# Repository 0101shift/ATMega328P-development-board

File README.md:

# ATMega328P-development-board
A development board designed to test ATMega328P Micro-controller which is similar to Arduino UNO. This was my very first Board design that i did in my college days.

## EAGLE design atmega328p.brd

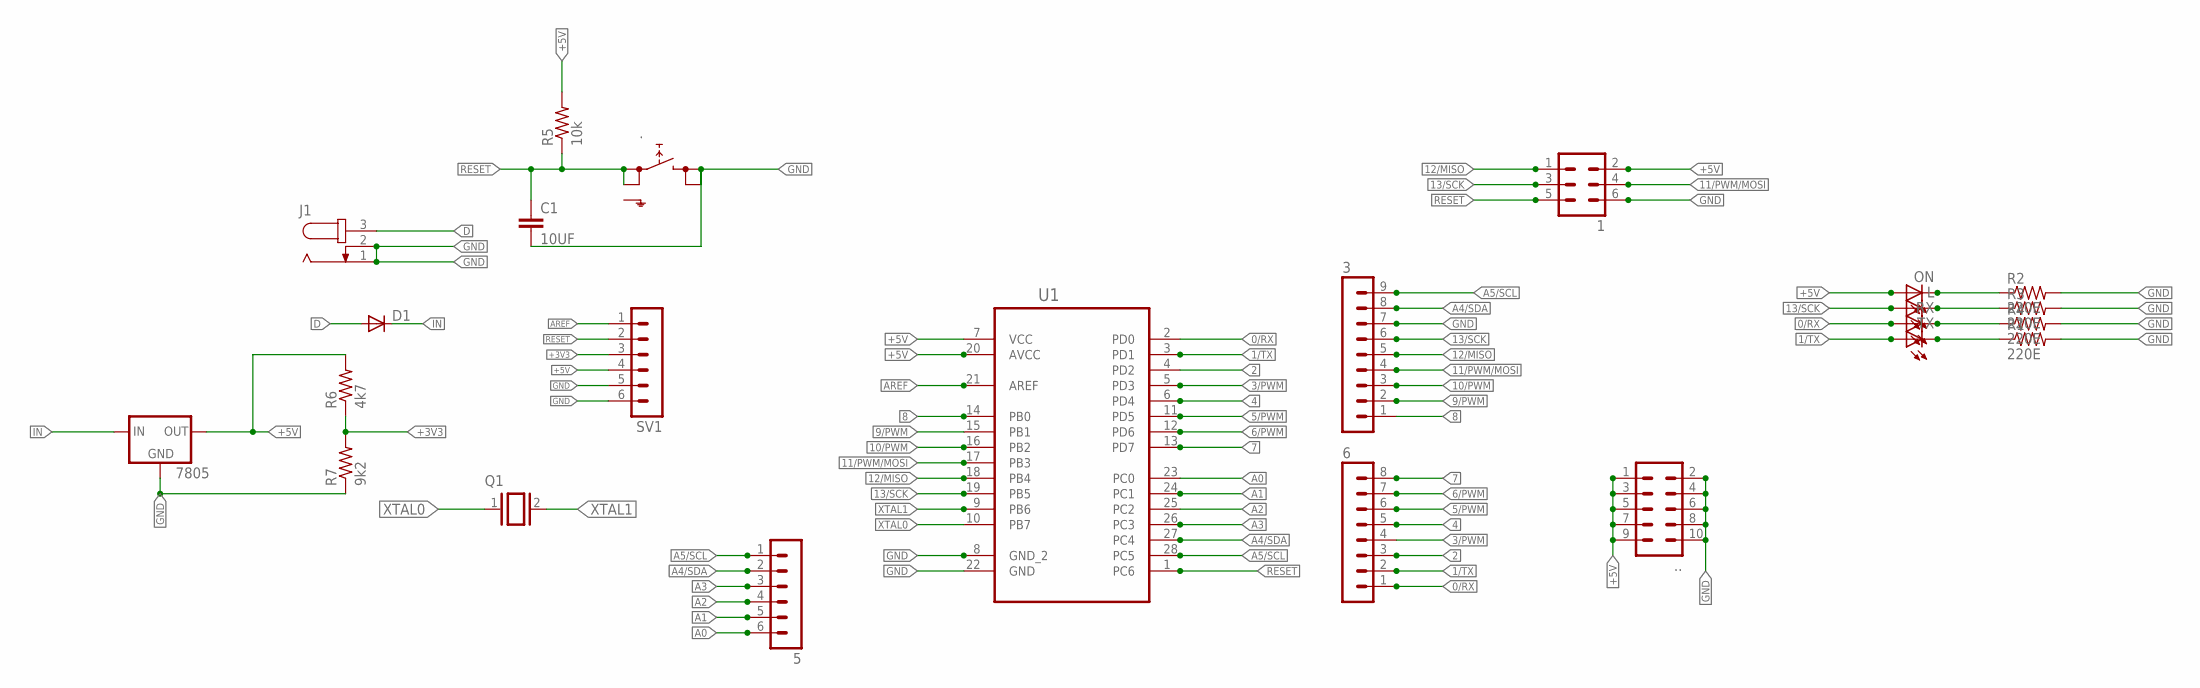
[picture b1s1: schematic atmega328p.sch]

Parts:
1: MA03-2
3: MA09-1
5: MA06-1
6: MA08-1
7805: 78XXS
.: SKHMPSE010; SKHMPXE010
..: MA05-2
C1: 10UF; C025-025X050
D1: 1N4004; DO41-10
J1: JACK-PLUG0; SPC4077
L: LEDCHIP-LED0805; CHIP-LED0805
ON: LEDCHIP-LED0805; CHIP-LED0805
Q1: XTAL/S; QS
R1, R2, R3, R4: 220E; 0204/7
R5: 10k; 0204/7
R6: 4k7; 0204/7
R7: 9k2; 0204/7
RX: LEDCHIP-LED0805; CHIP-LED0805
SV1: MA06-1
TX: LEDCHIP-LED0805; CHIP-LED0805
U1: ATMEGA328P-PU; DIP254P762X457-28

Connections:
0/RX: 6.1, RX.A, U1.2 (PD0)
1/TX: 6.2, TX.A, U1.3 (PD1)
2: 6.3, U1.4 (PD2)
3/PWM: 6.4, U1.5 (PD3)
4: 6.5, U1.6 (PD4)
5/PWM: 6.6, U1.11 (PD5)
6/PWM: 6.7, U1.12 (PD6)
7: 6.8, U1.13 (PD7)
8: 3.1, U1.14 (PB0)
9/PWM: 3.2, U1.15 (PB1)
10/PWM: 3.3, U1.16 (PB2)
11/PWM/MOSI: 1.4, 3.4, U1.17 (PB3)
12/MISO: 1.1, 3.5, U1.18 (PB4)
13/SCK: 1.3, 3.6, L.A, U1.19 (PB5)
+3V3: R6.1, R7.2, SV1.3
+5V: 1.2, 7805.OUT, ...1, ...3, ...5, ...7, ...9, ON.A, R5.2, R6.2, SV1.4, U1.7 (VCC), U1.20 (AVCC)
A0: 5.6, U1.23 (PC0)
A1: 5.5, U1.24 (PC1)
A2: 5.4, U1.25 (PC2)
A3: 5.3, U1.26 (PC3)
A4/SDA: 3.8, 5.2, U1.27 (PC4)
A5/SCL: 3.9, 5.1, U1.28 (PC5)
AREF: SV1.1, U1.21 (AREF)
D: D1.A, J1.3
GND: 1.6, 3.7, 7805.GND, ..3 (2.1), ..4 (2.2), ...2, ...4, ...6, ...8, ...10, C1.2, J1.1, J1.2, R1.2, R2.2, R3.2, R4.2, R7.1, SV1.5, SV1.6, U1.8 (GND_2), U1.22 (GND)
IN: 7805.IN, D1.C
unnamed: ON.C, R2.1
unnamed: L.C, R3.1
unnamed: R4.1, RX.C
unnamed: R1.1, TX.C
RESET: 1.5, ..1 (1.1), ..2 (1.2), C1.1, R5.1, SV1.2, U1.1 (PC6)
XTAL0: Q1.1, U1.10 (PB7)
XTAL1: Q1.2, U1.9 (PB6)

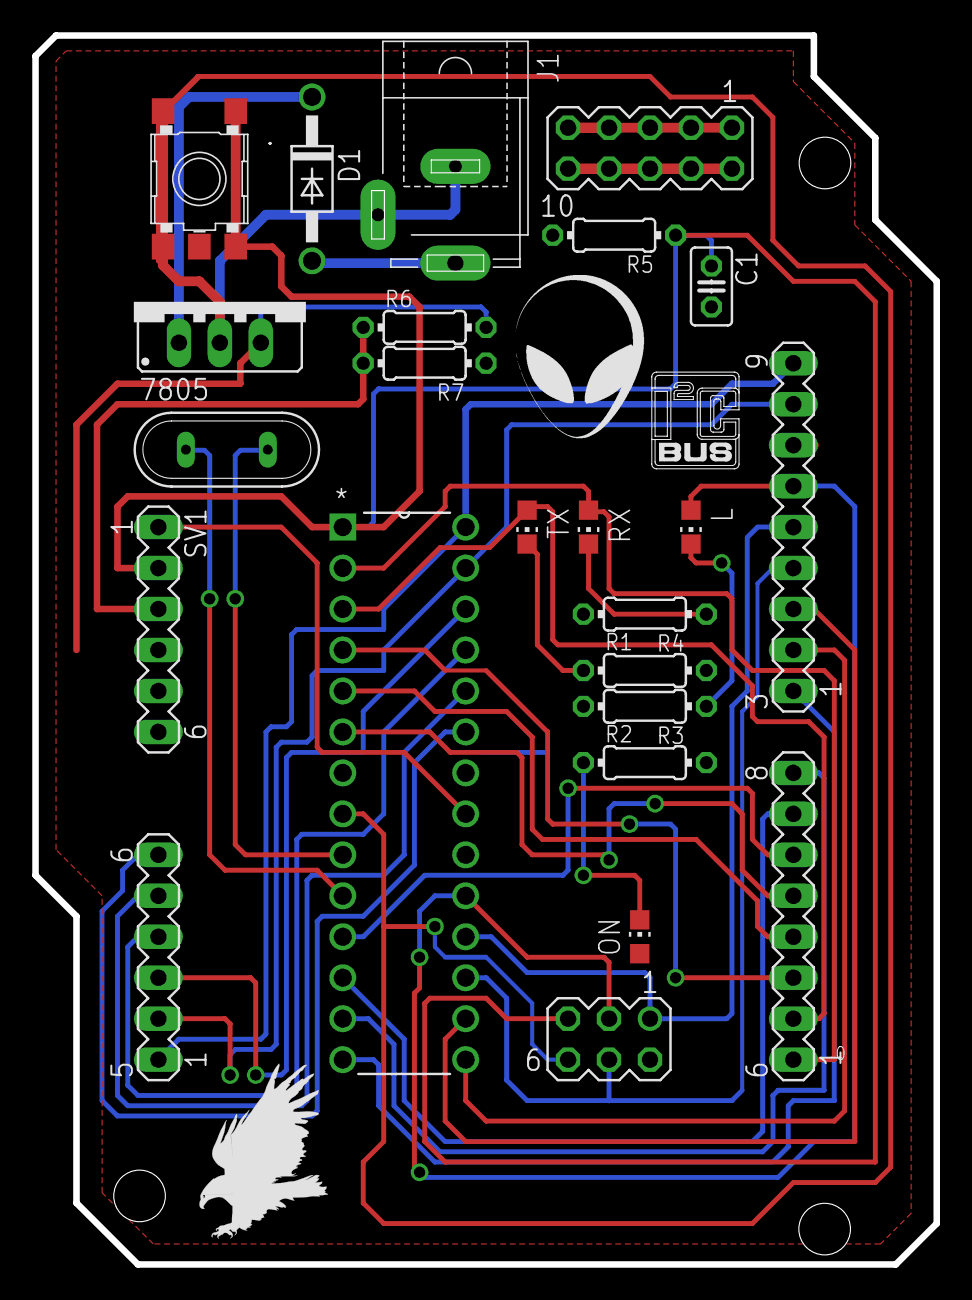
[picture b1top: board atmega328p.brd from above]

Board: 2 copper layers, 55.9 x 76.2 mm, 26 parts (0 on the bottom side), 33 nets.

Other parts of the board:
U$2: I2C
U$4: EAGLE-PLC-8MM

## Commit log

2022-06-18 Add files via upload
    Added Project Design files
2022-06-18 Update README.md
    Added Images
